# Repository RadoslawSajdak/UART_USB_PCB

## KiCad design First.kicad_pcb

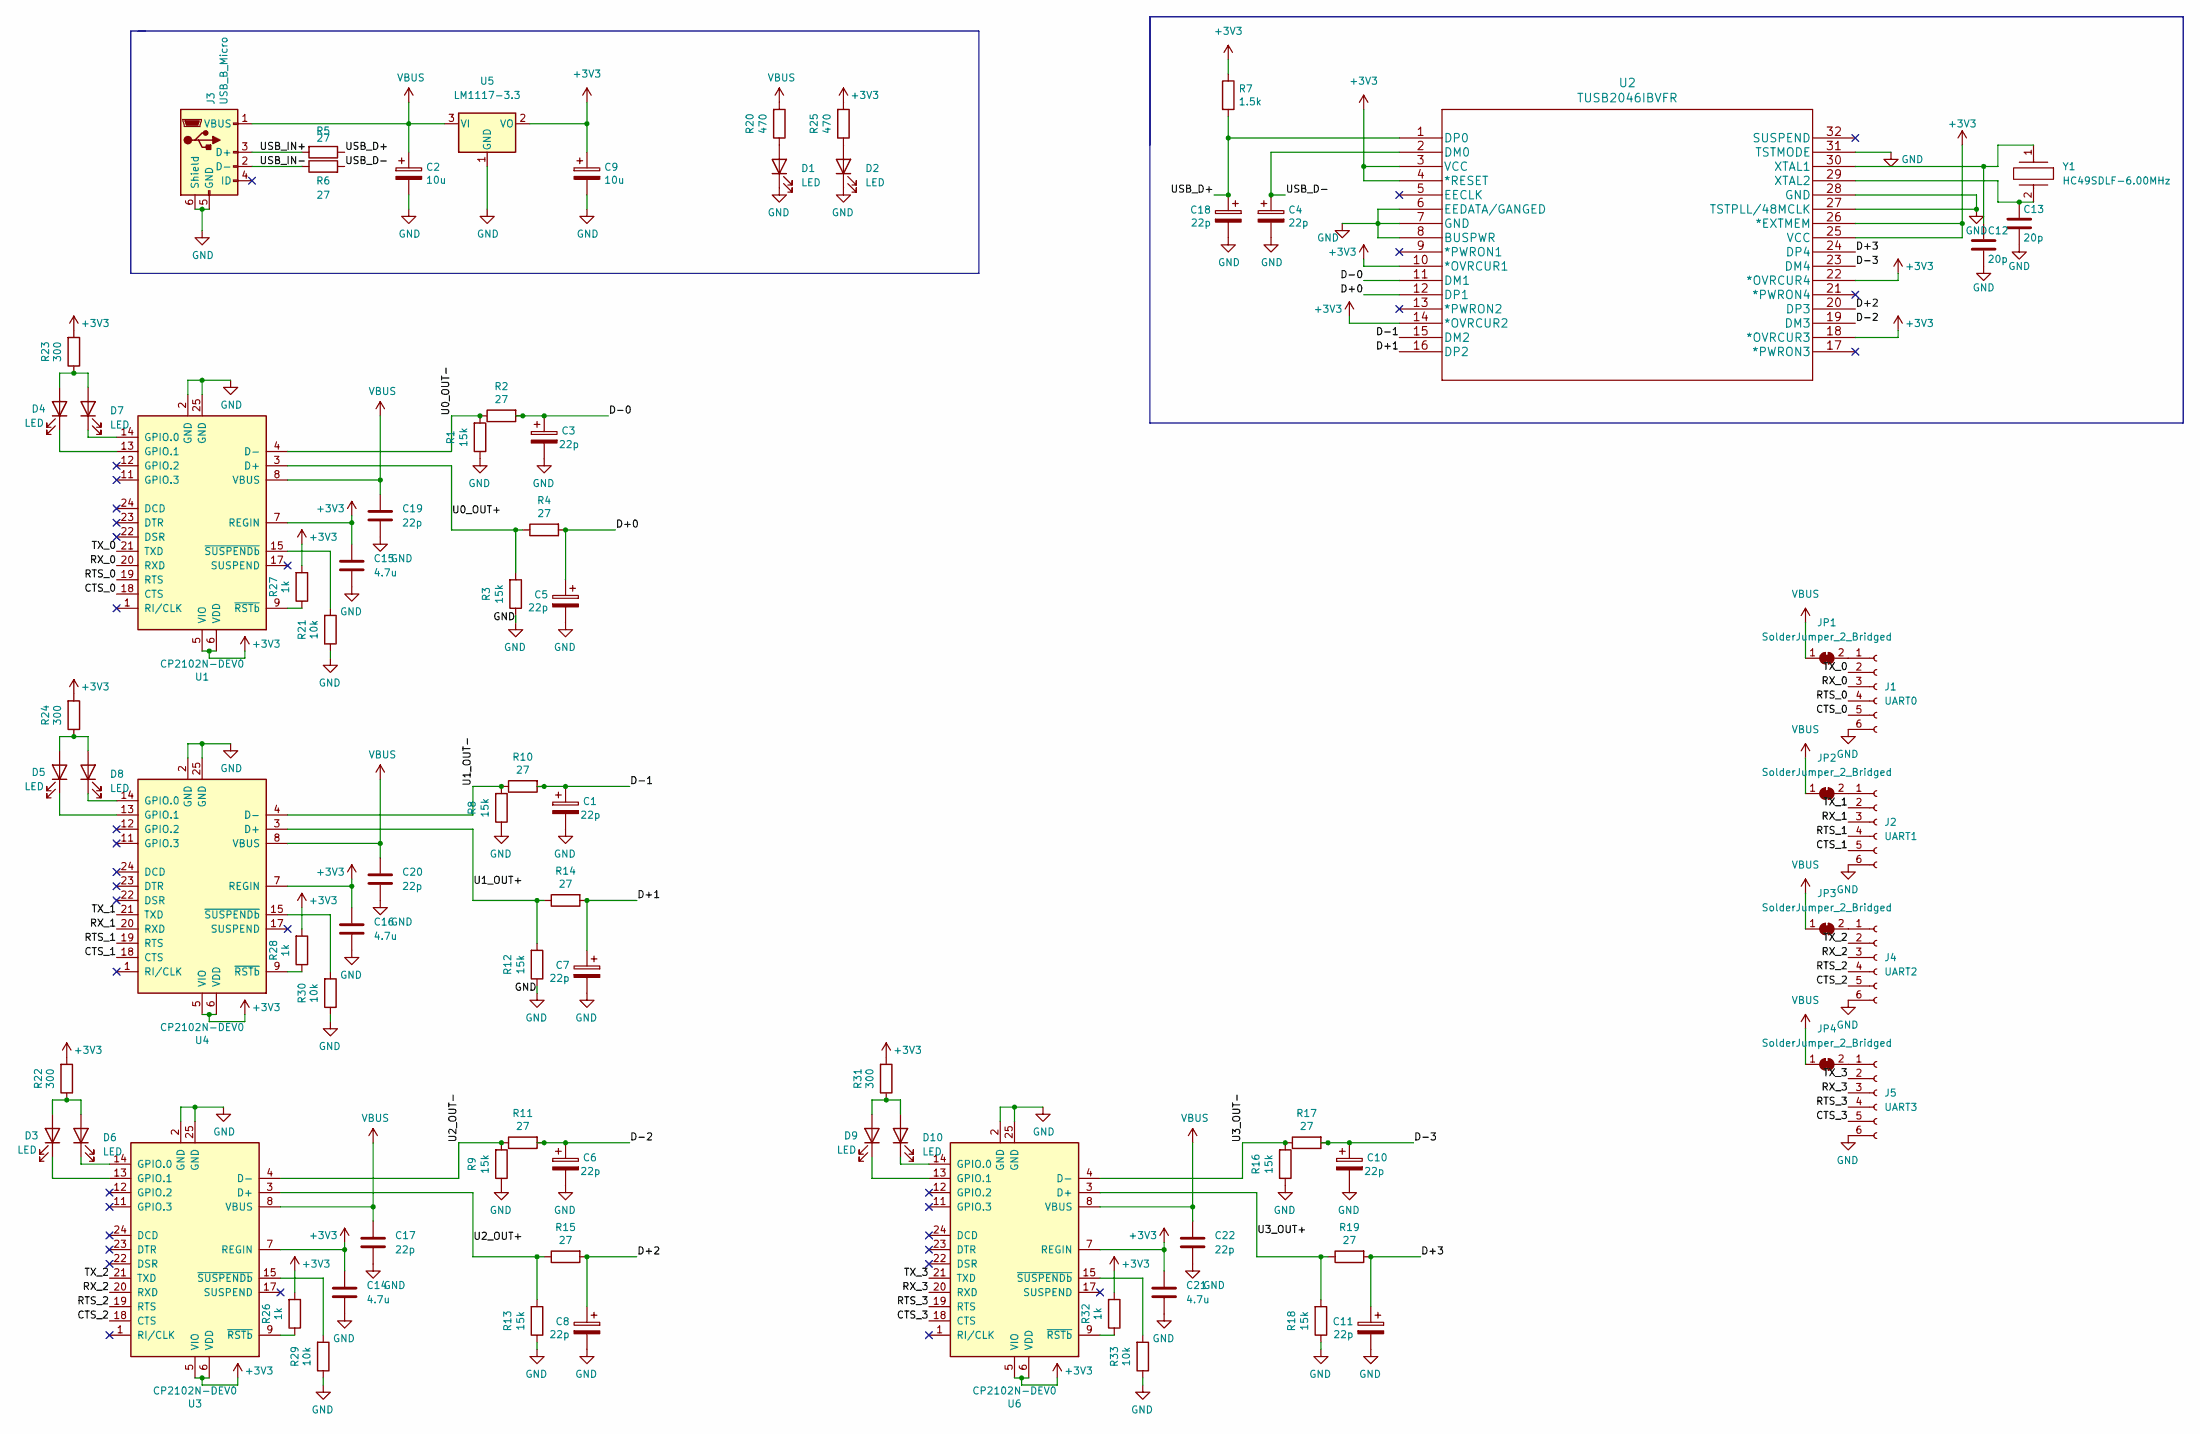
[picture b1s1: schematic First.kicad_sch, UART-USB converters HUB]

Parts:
C1, C3, C4, C5, C6, C7, C8, C10, C11, C17, C18, C19, C20, C22: 22p; C_0603_1608Metric
C2, C9: 10u; C_0603_1608Metric
C12, C13: 20p; C_0603_1608Metric
C14, C15, C16, C21: 4.7u; C_0603_1608Metric
D1, D2, D3, D4, D5, D6, D7, D8, D9, D10: LED; LED_0805_2012Metric
J1: UART0; PinSocket_1x06_P2.54mm_Vertical
J2: UART1; PinSocket_1x06_P2.54mm_Vertical
J3: USB_B_Micro; USB_Micro-B_Molex-105017-0001
J4: UART2; PinSocket_1x06_P2.54mm_Vertical
J5: UART3; PinSocket_1x06_P2.54mm_Vertical
JP1, JP2, JP3, JP4: SolderJumper_2_Bridged; SolderJumper-2_P1.3mm_Bridged_RoundedPad1.0x1.5mm
R1, R3, R8, R9, R12, R13, R16, R18: 15k; R_0603_1608Metric
R2, R4, R5, R6, R10, R11, R14, R15, R17, R19: 27; R_0603_1608Metric
R7: 1.5k; R_0603_1608Metric
R20, R25: 470; R_0603_1608Metric
R21, R29, R30, R33: 10k; R_0603_1608Metric
R22, R23, R24, R31: 300; R_0603_1608Metric
R26, R27, R28, R32: 1k; R_0603_1608Metric
U1, U3, U4, U6: CP2102N-DEV0; QFN50P400X400X80-25N
U2: TUSB2046IBVFR
U5: LM1117-3.3; SOT-223
Y1: HC49SDLF-6.00MHz; HC49SDLF800MHz; Manufacturer_Part_Number HC49SDLF-8.00MHz; Mouser Part Number 559-FOXSDLF/080-12

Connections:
+3V3: C9.1, C14.1, C15.1, C16.1, C21.1, R7.1, R22.2, R23.2, R24.2, R25.2, R26.2, R27.2, R28.2, R31.2, R32.2, U1.5 (VIO), U1.6 (VDD), U1.7 (REGIN), U2.3 (VCC), U2.4 (*RESET), U2.10 (*OVRCUR1), U2.14 (*OVRCUR2), U2.18 (*OVRCUR3), U2.22 (*OVRCUR4), U2.25 (VCC), U2.26 (*EXTMEM), U3.5 (VIO), U3.6 (VDD), U3.7 (REGIN), U4.5 (VIO), U4.6 (VDD), U4.7 (REGIN), U5.2 (VO), U6.5 (VIO), U6.6 (VDD), U6.7 (REGIN)
/CTS_0: J1.5, U1.18 (CTS)
/CTS_1: J2.5, U4.18 (CTS)
/CTS_2: J4.5, U3.18 (CTS)
/CTS_3: J5.5, U6.18 (CTS)
/D+0: C5.1, R4.2, U2.12 (DP1)
/D+1: C7.1, R14.2, U2.16 (DP2)
/D+2: C8.1, R15.2, U2.20 (DP3)
/D+3: C11.1, R19.2, U2.24 (DP4)
/D-0: C3.1, R2.2, U2.11 (DM1)
/D-1: C1.1, R10.2, U2.15 (DM2)
/D-2: C6.1, R11.2, U2.19 (DM3)
/D-3: C10.1, R17.2, U2.23 (DM4)
/RTS_0: J1.4, U1.19 (RTS)
/RTS_1: J2.4, U4.19 (RTS)
/RTS_2: J4.4, U3.19 (RTS)
/RTS_3: J5.4, U6.19 (RTS)
/RX_0: J1.3, U1.20 (RXD)
/RX_1: J2.3, U4.20 (RXD)
/RX_2: J4.3, U3.20 (RXD)
/RX_3: J5.3, U6.20 (RXD)
/TX_0: J1.2, U1.21 (TXD)
/TX_1: J2.2, U4.21 (TXD)
/TX_2: J4.2, U3.21 (TXD)
/TX_3: J5.2, U6.21 (TXD)
/U0_OUT+: R3.2, R4.1, U1.3 (D+)
/U0_OUT-: R1.2, R2.1, U1.4 (D-)
/U1_OUT+: R12.2, R14.1, U4.3 (D+)
/U1_OUT-: R8.2, R10.1, U4.4 (D-)
/U2_OUT+: R13.2, R15.1, U3.3 (D+)
/U2_OUT-: R9.2, R11.1, U3.4 (D-)
/U3_OUT+: R18.2, R19.1, U6.3 (D+)
/U3_OUT-: R16.2, R17.1, U6.4 (D-)
/USB_D+: C18.1, R5.1, R7.2, U2.1 (DP0)
/USB_D-: C4.1, R6.2, U2.2 (DM0)
/USB_IN+: J3.3 (D+), R5.2
/USB_IN-: J3.2 (D-), R6.1
GND: C1.2, C2.2, C3.2, C4.2, C5.2, C6.2, C7.2, C8.2, C9.2, C10.2, C11.2, C12.2, C13.2, C14.2, C15.2, C16.2, C17.2, C18.2, C19.2, C20.2, C21.2, C22.2, D1.1 (K), D2.1 (K), J1.6, J2.6, J3.5 (GND), J3.6 (Shield), J4.6, J5.6, R1.1, R3.1, R8.1, R9.1, R12.1, R13.1, R16.1, R18.1, R21.1, R29.1, R30.1, R33.1, U1.2 (GND), U1.25 (GND), U2.6 (EEDATA/GANGED), U2.7 (GND), U2.8 (BUSPWR), U2.27 (TSTPLL/48MCLK), U2.28 (GND), U2.31 (TSTMODE), U3.2 (GND), U3.25 (GND), U4.2 (GND), U4.25 (GND), U5.1 (GND), U6.2 (GND), U6.25 (GND)
unnamed: C12.1, U2.30 (XTAL1), Y1.1
unnamed: C13.1, U2.29 (XTAL2), Y1.2
unnamed: D1.2 (A), R20.1
unnamed: D2.2 (A), R25.1
unnamed: D3.1 (K), U3.13 (GPIO.1)
unnamed: D3.2 (A), D6.2 (A), R22.1
unnamed: D4.1 (K), U1.13 (GPIO.1)
unnamed: D4.2 (A), D7.2 (A), R23.1
unnamed: D5.1 (K), U4.13 (GPIO.1)
unnamed: D5.2 (A), D8.2 (A), R24.1
unnamed: D6.1 (K), U3.14 (GPIO.0)
unnamed: D7.1 (K), U1.14 (GPIO.0)
unnamed: D8.1 (K), U4.14 (GPIO.0)
unnamed: D9.1 (K), U6.13 (GPIO.1)
unnamed: D10.1 (K), U6.14 (GPIO.0)
unnamed: D9.2 (A), D10.2 (A), R31.1
unnamed: J1.1, JP1.2 (B)
unnamed: J2.1, JP2.2 (B)
unnamed: J4.1, JP3.2 (B)
unnamed 57: J5.1, JP4.2 (B); also elsewhere on the board
unnamed: R21.2, U1.15 (~SUSPENDb)
unnamed: R26.1, U3.9 (~RSTb)
unnamed: R27.1, U1.9 (~RSTb)
unnamed: R28.1, U4.9 (~RSTb)
unnamed: R29.2, U3.15 (~SUSPENDb)
unnamed: R30.2, U4.15 (~SUSPENDb)
unnamed: R32.1, U6.9 (~RSTb)
unnamed: R33.2, U6.15 (~SUSPENDb)
VBUS: C2.1, C17.1, C19.1, C20.1, C22.1, J3.1 (VBUS), JP1.1 (A), JP2.1 (A), JP3.1 (A), JP4.1 (A), R20.2, U1.8 (VBUS), U3.8 (VBUS), U4.8 (VBUS), U5.3 (VI), U6.8 (VBUS); also elsewhere on the board

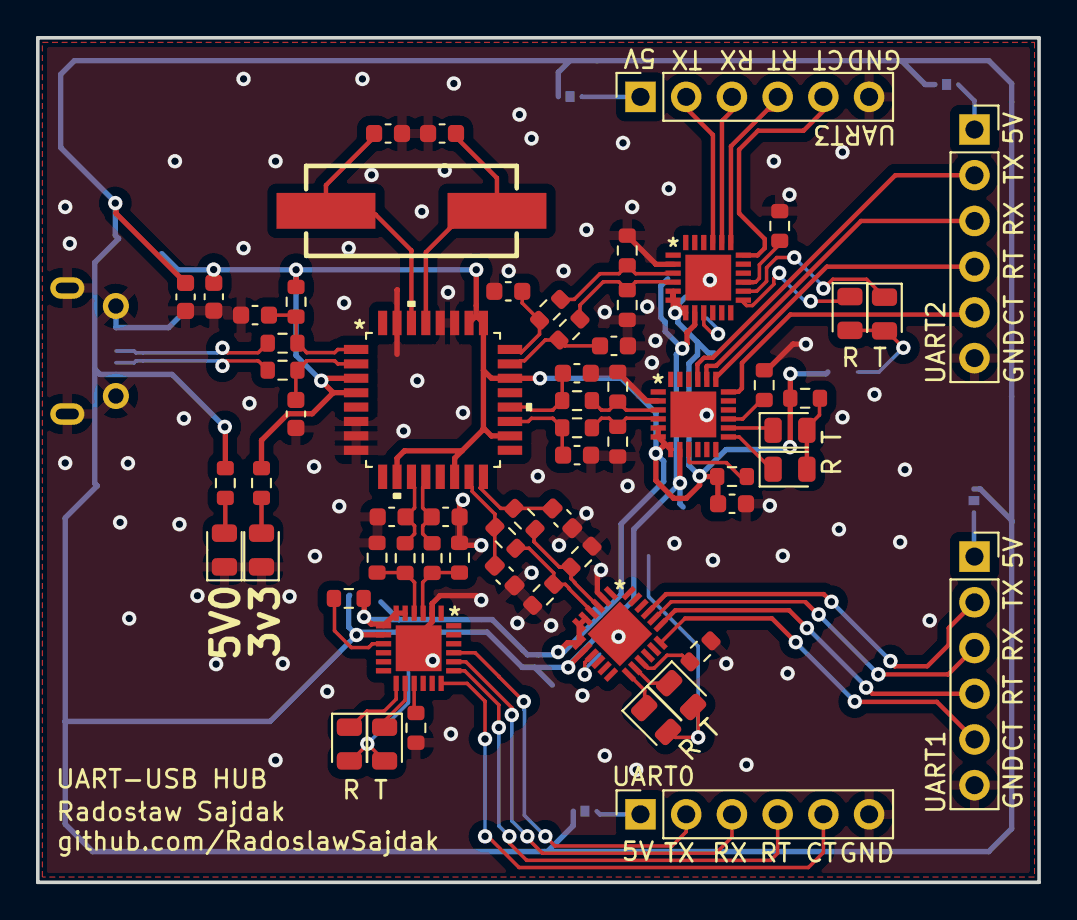
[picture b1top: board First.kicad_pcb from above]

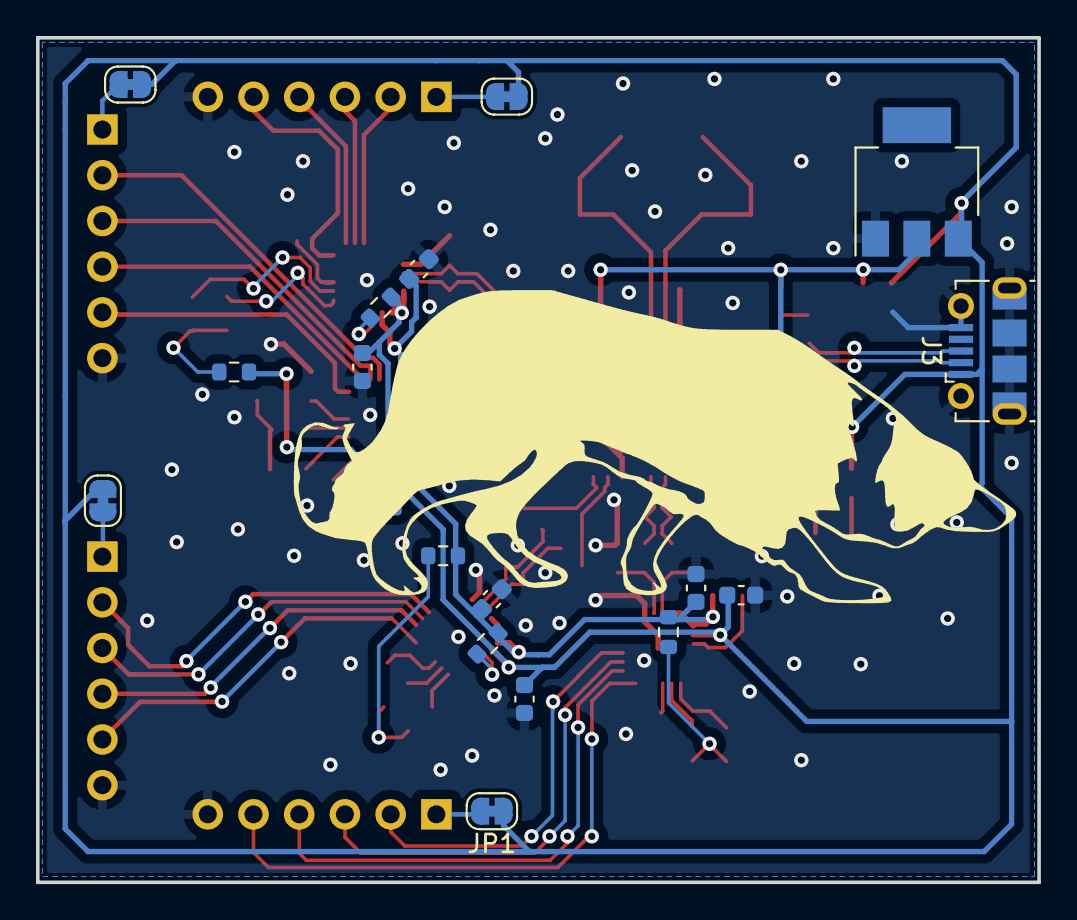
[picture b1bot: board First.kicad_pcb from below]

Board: 2 copper layers, 55.6 x 46.9 mm, 81 parts (18 on the bottom side), 67 nets.

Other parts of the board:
5V_ON: SolderJumper_2_Bridged; SolderJumper-2_P1.3mm_Bridged_RoundedPad1.0x1.5mm

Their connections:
unnamed 57: 5V_ON.2 (B); also elsewhere on the board
VBUS: 5V_ON.1 (A); also elsewhere on the board

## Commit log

2021-10-13 First version of the PCB
2022-08-21 Totally new version
2022-08-22 Ordered version
2022-10-04 Final and tested version
2022-10-07 Second review

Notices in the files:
parts and their libraries:
Copyright 2021 Accelerated Designs. All rights reserved.
